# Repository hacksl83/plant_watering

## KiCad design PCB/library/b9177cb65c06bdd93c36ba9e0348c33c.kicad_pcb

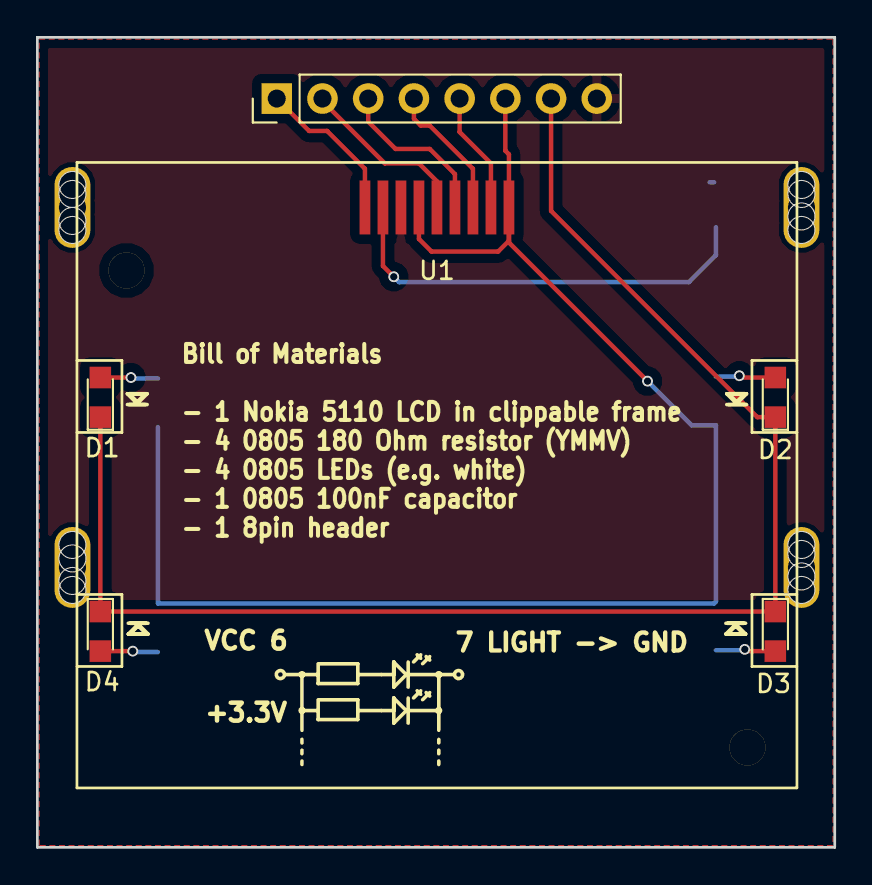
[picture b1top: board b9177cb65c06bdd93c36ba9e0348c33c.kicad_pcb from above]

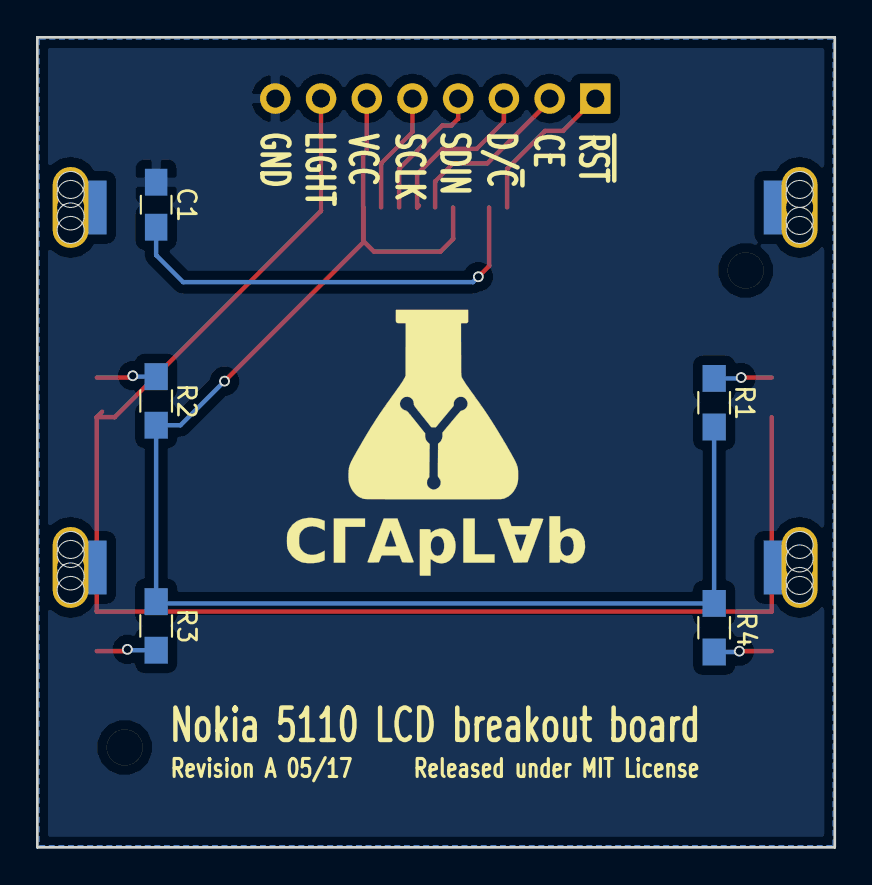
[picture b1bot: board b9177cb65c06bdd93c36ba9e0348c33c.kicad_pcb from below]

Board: 2 copper layers, 44.3 x 45.0 mm, 11 parts (5 on the bottom side), 13 nets.

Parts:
C1: 100n; C_0805_HandSoldering
D1, D2, D3, D4: LED; LED_0805
P1: CONN_01X08; Pin_Header_Straight_1x08_Pitch2.54mm
R1, R2, R3, R4: R; R_0805_HandSoldering
U1: Nokia_5110_LCD; Nokia_5110-3310_LCD

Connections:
GND: C1.2, P1.8, U1.3
unnamed: C1.1, U1.2
unnamed: D1.1, D2.1, D3.1, D4.1, P1.7
unnamed: D1.2, R1.1
unnamed: D2.2, R2.1
unnamed: D3.2, R3.1
unnamed: D4.2, R4.1
unnamed: P1.1, U1.1
unnamed: P1.2, U1.5
unnamed: P1.3, U1.6
unnamed: P1.4, U1.7
unnamed: P1.5, U1.8
unnamed: P1.6, R1.2, R2.2, R3.2, R4.2, U1.4, U1.9

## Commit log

2025-01-25 Add the project source code files and datasheets
2025-01-25 add .gitignore file
2025-01-25 Fix path in .gitignore file
2025-01-25 Adding the PCB layout files

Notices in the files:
PCB/library/b9177cb65c06bdd93c36ba9e0348c33c.kicad_pcb:
Revision A 05/17 Released under MIT License
